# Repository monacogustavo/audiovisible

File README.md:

# audiovisible
An Audiovisual Spectrum Analyzer, for an Underserved Audience

# Features
## CORE
Multi-color display
Audio output

## ADVANCED
Waveform Simulation
Graphic Equalization

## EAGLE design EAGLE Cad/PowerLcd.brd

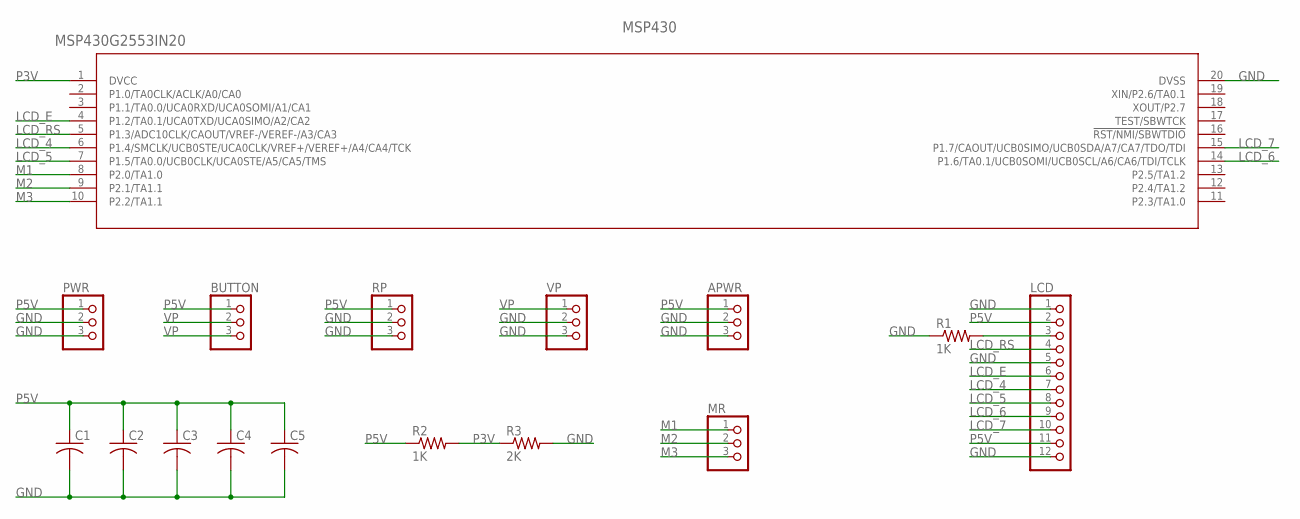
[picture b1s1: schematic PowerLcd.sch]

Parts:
APWR: PINHD-1X3; 1X03
BUTTON: PINHD-1X3; 1X03
C1, C2, C3, C4, C5: C-US075-042X103; C075-042X103
LCD: PINHD-1X12; 1X12
MR: PINHD-1X3; 1X03
MSP430: MSP430G2553IN20; N20_TEX
PWR: PINHD-1X3; 1X03
R1, R2: 1K; 0204/5
R3: 2K; 0204/5
RP: PINHD-1X3; 1X03
VP: PINHD-1X3; 1X03

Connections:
GND: APWR.2, APWR.3, C1.2, C2.2, C3.2, C4.2, C5.2, LCD.1, LCD.5, LCD.12, MSP430.20 (DVSS), PWR.2, PWR.3, R1.1, R3.2, RP.2, RP.3, VP.2, VP.3
LCD_4: LCD.7, MSP430.6 (P1.4/SMCLK/UCB0STE/UCA0CLK/VREF+/VEREF+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)
LCD_5: LCD.8, MSP430.7 (P1.5/TA0.0/UCB0CLK/UCA0STE/A5/CA5/TMS)
LCD_6: LCD.9, MSP430.14 (P1.6/TA0.1/UCB0SOMI/UCB0SCL/A6/CA6/TDI/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)
LCD_7: LCD.10, MSP430.15 (P1.7/CAOUT/UCB0SIMO/UCB0SDA/A7/CA7/TDO/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)
LCD_E: LCD.6, MSP430.4 (P1.2/TA0.1/UCA0TXD/UCA0SIMO/A2/CA2)
LCD_RS: LCD.4, MSP430.5 (P1.3/ADC10CLK/CAOUT/VREF-/VEREF-/A3/CA3)
M1: MR.1, MSP430.8 (P2.0/TA1.0)
M2: MR.2, MSP430.9 (P2.1/TA1.1)
M3: MR.3, MSP430.10 (P2.2/TA1.1)
unnamed: LCD.3, R1.2
P3V: MSP430.1 (DVCC), R2.2, R3.1
P5V: APWR.1, BUTTON.1, C1.1, C2.1, C3.1, C4.1, C5.1, LCD.2, LCD.11, PWR.1, R2.1, RP.1
VP: BUTTON.2, BUTTON.3, VP.1

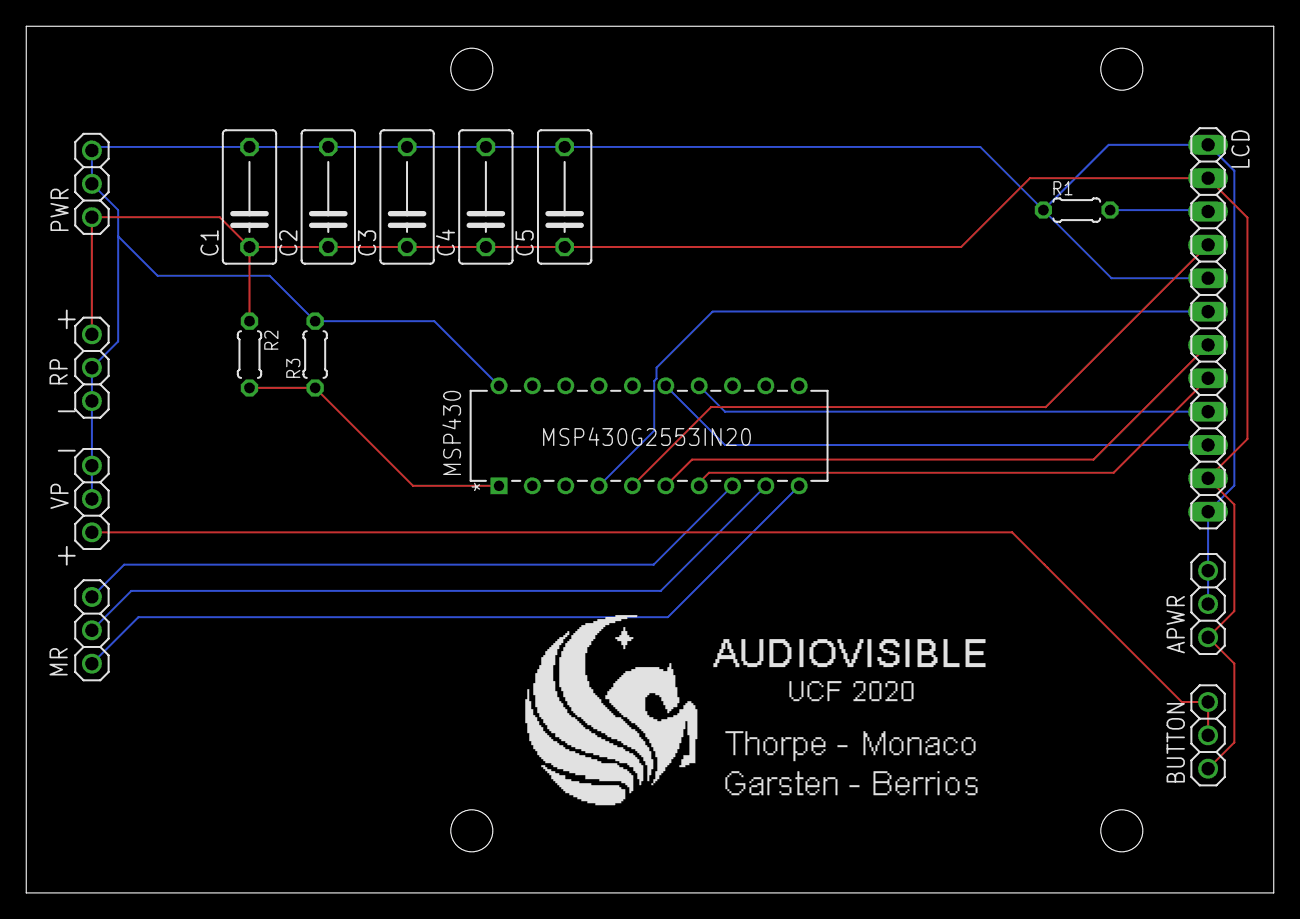
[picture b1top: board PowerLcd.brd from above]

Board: 2 copper layers, 95.0 x 66.0 mm, 20 parts (0 on the bottom side), 14 nets.

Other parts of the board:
U$1, U$2, U$7, U$8: 3_2_HOLE

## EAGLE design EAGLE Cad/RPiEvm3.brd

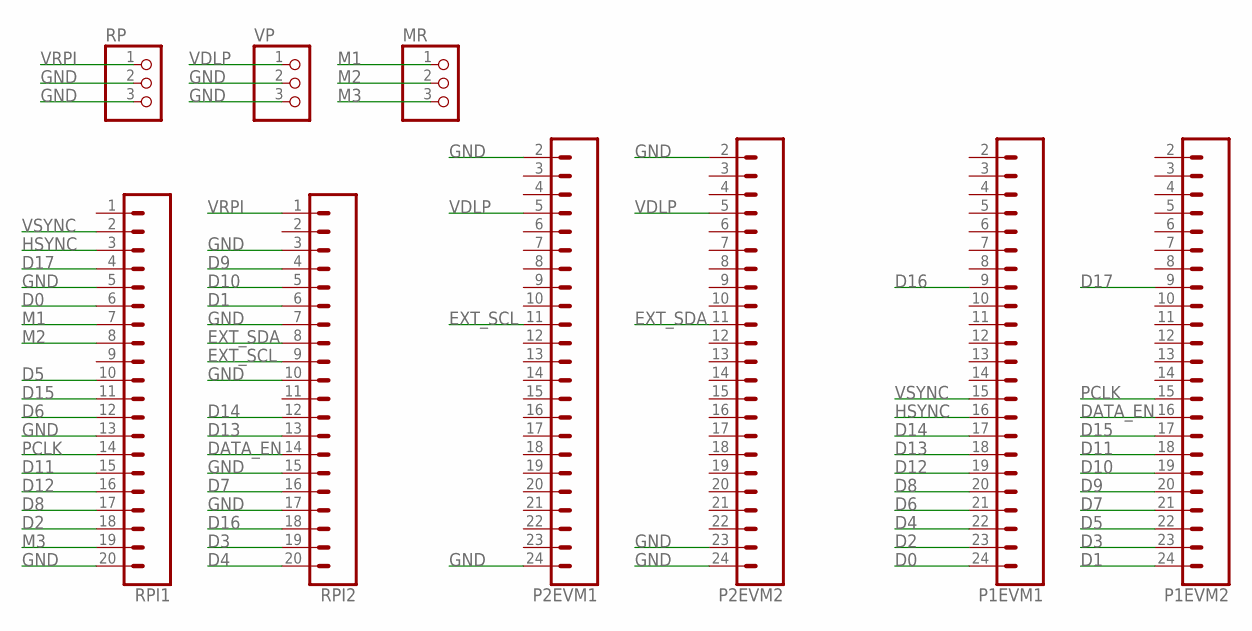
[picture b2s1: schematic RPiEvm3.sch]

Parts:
MR: PINHD-1X3; 1X03
P1EVM1, P1EVM2, P2EVM1, P2EVM2: CONN_23; 1X23
RP: PINHD-1X3; 1X03
RPI1, RPI2: CONN_20; 1X20
VP: PINHD-1X3; 1X03

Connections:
D0: P1EVM1.24, RPI1.6
D1: P1EVM2.24, RPI2.6
D2: P1EVM1.23, RPI1.18
D3: P1EVM2.23, RPI2.19
D4: P1EVM1.22, RPI2.20
D5: P1EVM2.22, RPI1.10
D6: P1EVM1.21, RPI1.12
D7: P1EVM2.21, RPI2.16
D8: P1EVM1.20, RPI1.17
D9: P1EVM2.20, RPI2.4
D10: P1EVM2.19, RPI2.5
D11: P1EVM2.18, RPI1.15
D12: P1EVM1.19, RPI1.16
D13: P1EVM1.18, RPI2.13
D14: P1EVM1.17, RPI2.12
D15: P1EVM2.17, RPI1.11
D16: P1EVM1.9, RPI2.18
D17: P1EVM2.9, RPI1.4
DATA_EN: P1EVM2.16, RPI2.14
EXT_SCL: P2EVM1.11, RPI2.9
EXT_SDA: P2EVM2.11, RPI2.8
GND: P2EVM1.2, P2EVM1.24, P2EVM2.2, P2EVM2.23, P2EVM2.24, RP.2, RP.3, RPI1.5, RPI1.13, RPI1.20, RPI2.3, RPI2.7, RPI2.10, RPI2.15, RPI2.17, VP.2, VP.3
HSYNC: P1EVM1.16, RPI1.3
M1: MR.1, RPI1.7
M2: MR.2, RPI1.8
M3: MR.3, RPI1.19
PCLK: P1EVM2.15, RPI1.14
VDLP: P2EVM1.5, P2EVM2.5, VP.1
VRPI: RP.1, RPI2.1
VSYNC: P1EVM1.15, RPI1.2

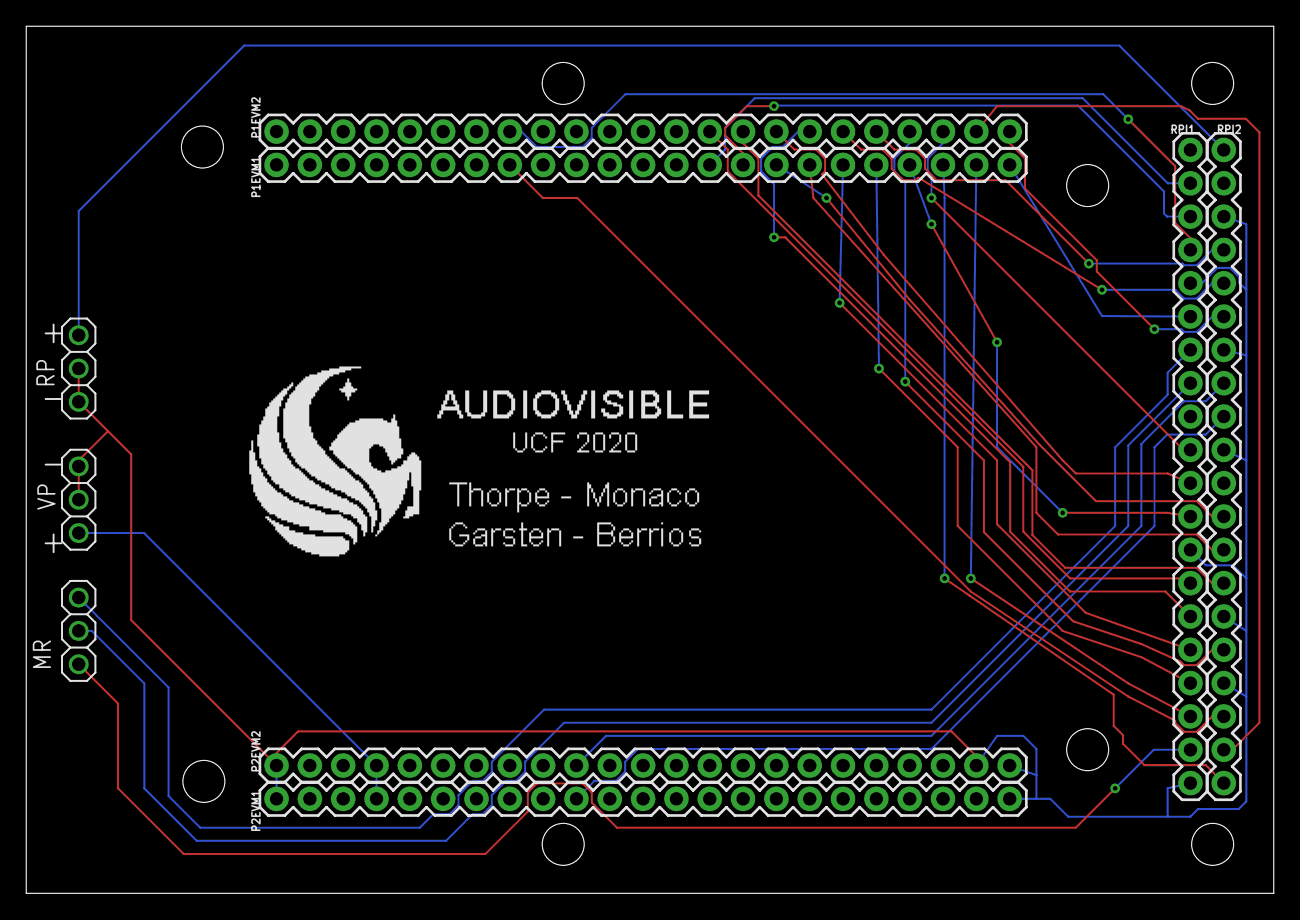
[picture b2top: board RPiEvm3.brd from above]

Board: 2 copper layers, 95.1 x 66.1 mm, 17 parts (0 on the bottom side), 30 nets.

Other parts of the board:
U$1, U$2, U$3, U$4, U$5, U$6, U$7, U$8: 3_2_HOLE

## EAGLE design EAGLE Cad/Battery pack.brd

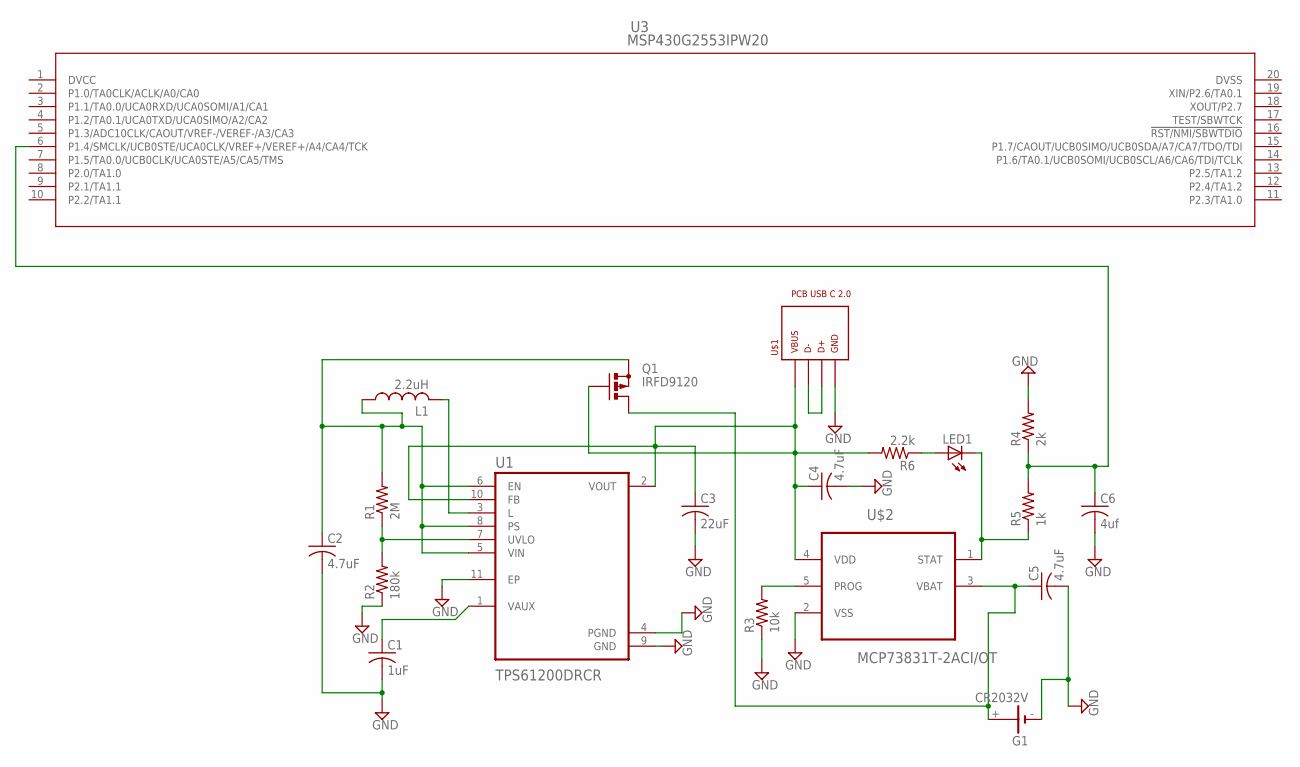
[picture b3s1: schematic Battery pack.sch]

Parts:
C1: 1uF; C150-064X183
C2, C4, C5: 4.7uF; C150-064X183
C3: 22uF; C150-064X183
C6: 4uf; C150-064X183
G1: CR2032V
L1: 2.2uH; 0207/15
LED1: LEDB155; Q62902-B155
Q1: IRFD9120; C370-01
R1: 2M; 0207/15
R2: 180k; 0207/15
R3: 10k; 0207/15
R4: 2k; 0207/15
R5: 1k; 0207/15
R6: 2.2k; 0207/15
U1: TPS61200DRCR; VREG_V62/16624-01YE
U3: MSP430G2553IPW20; PW20
U$1: PCB_USB_C_2.0DS_1; USB_TYPE_C_DS_1
U$2: MCP73831T-2ACI/OT; SOT95P280X145-5N

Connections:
DVCC: U3.1 (DVCC)
DVSS: U3.20 (DVSS)
GND: C1.2, C2.2, C3.2, C4.2, C5.2, C6.2, G1.-, R2.1, R3.1, R4.2, U1.4 (PGND), U1.9 (GND), U1.11 (EP), U$1.A1 (GND), U$1.A12 (GND), U$1.B1 (GND), U$1.B12 (GND), U$2.2 (VSS)
unnamed: R1.1, R2.2, U1.7 (UVLO)
unnamed: C3.1, C4.1, Q1.G, R6.2, U1.2 (VOUT), U1.10 (FB), U$1.A4 (VBUS), U$1.A9 (VBUS), U$1.B4 (VBUS), U$1.B9 (VBUS), U$2.4 (VDD)
unnamed: C2.1, L1.1, Q1.S, R1.2, U1.5 (VIN), U1.6 (EN), U1.8 (PS)
unnamed: C1.1, U1.1 (VAUX)
unnamed: L1.2, U1.3 (L)
unnamed: U$1.A6 (D+), U$1.A7 (D-), U$1.B6 (D+), U$1.B7 (D-)
unnamed: R3.2, U$2.5 (PROG)
unnamed: LED1.K (C), R5.1, U$2.1 (STAT)
unnamed: C6.1, R4.1, R5.2, U3.6 (P1.4/SMCLK/UCB0STE/UCA0CLK/VREF+/VEREF+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)
unnamed: LED1.A, R6.1
unnamed: C5.1, G1.+, Q1.D, Q1.D1 (D), U$2.3 (VBAT)

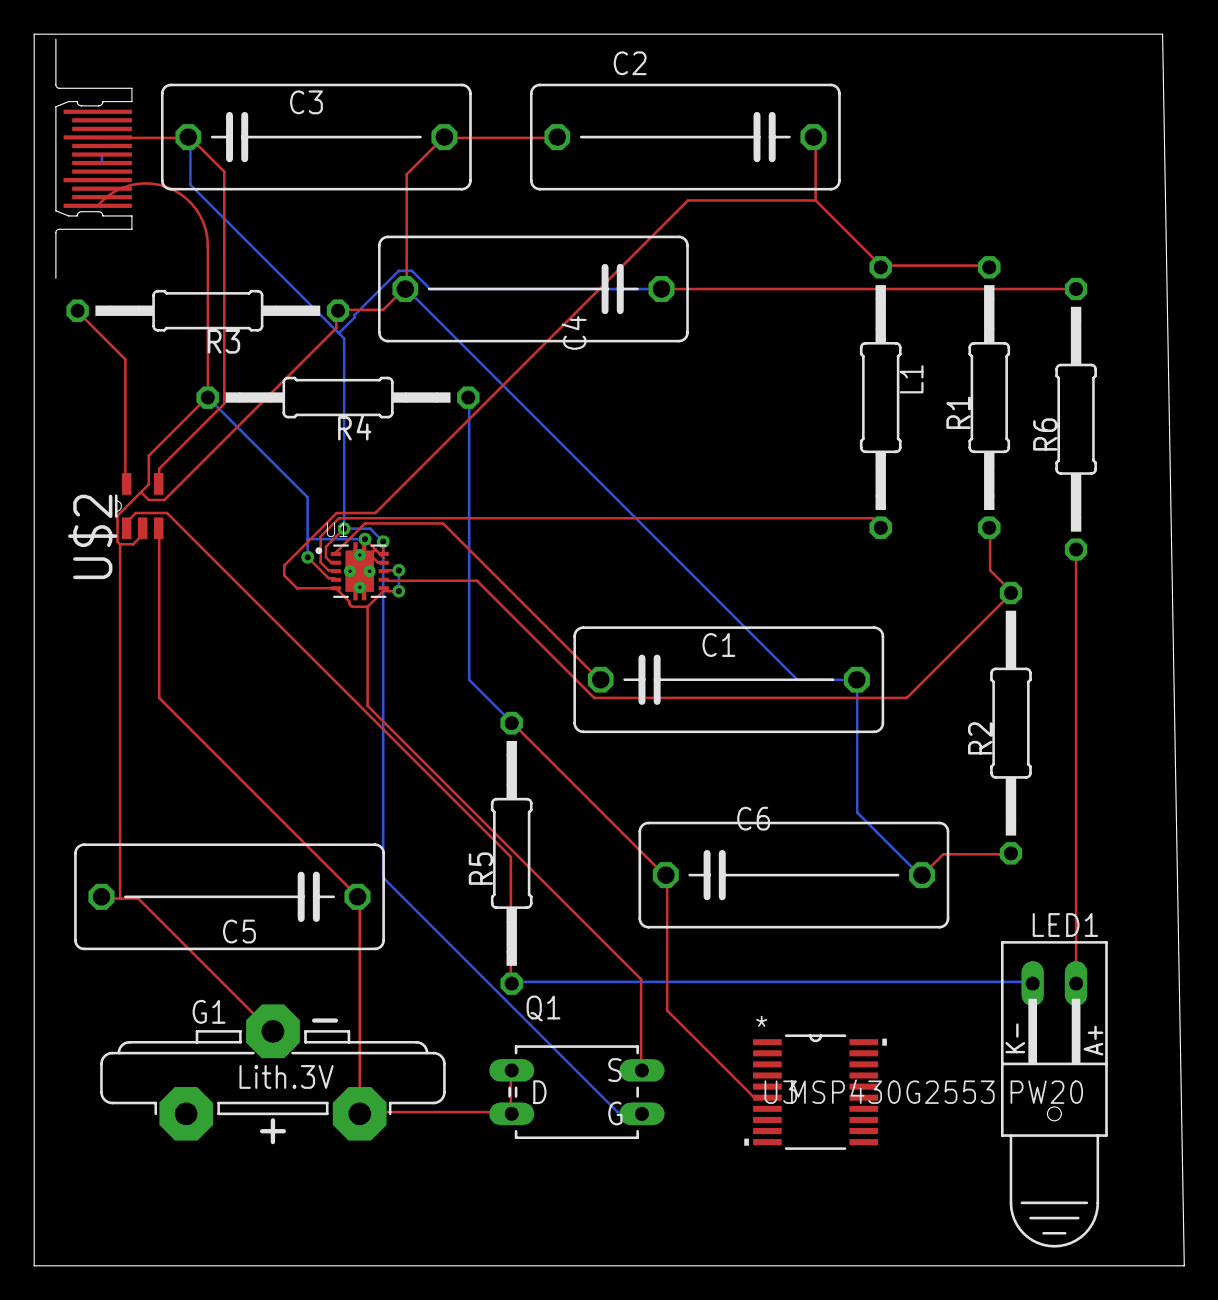
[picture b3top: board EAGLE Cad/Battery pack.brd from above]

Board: 2 copper layers, 67.3 x 72.1 mm, 20 parts (0 on the bottom side), 12 nets.

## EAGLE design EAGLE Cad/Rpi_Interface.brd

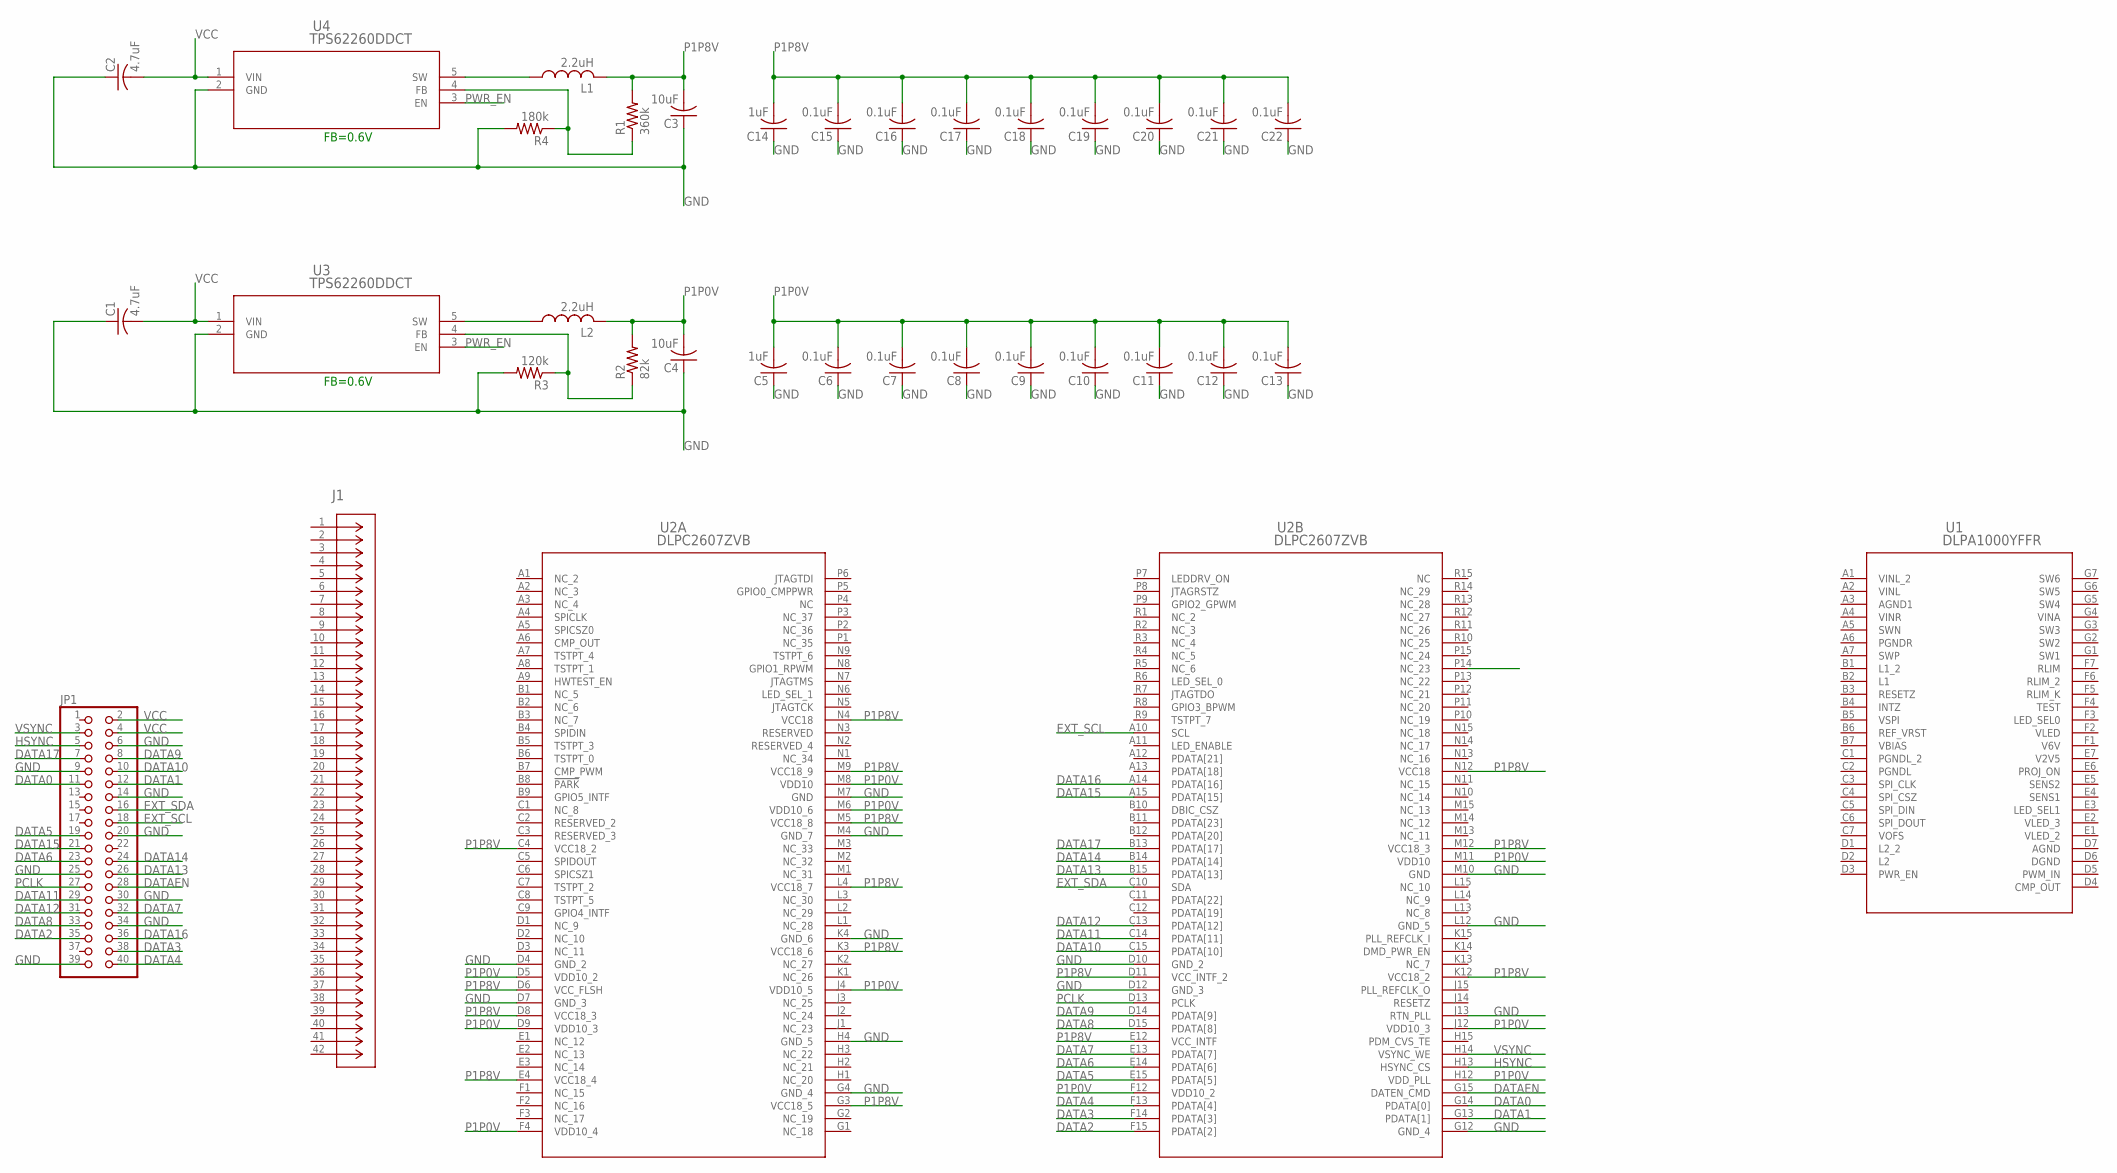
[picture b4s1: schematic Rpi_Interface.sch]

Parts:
C1, C2: 4.7uF; C0201
C3, C4: 10uF; C0201
C5, C14: 1uF; C0201
C6, C7, C8, C9, C10, C11, C12, C13, C15, C16, C17, C18, C19, C20, C21, C22: 0.1uF; C0201
J1: AXT642124DD1; CONN_AXT642124_PAN
JP1: PINHD-2X20; 2X20
L1, L2: 2.2uH; L0201
R1: 360k; 0204V
R2: 82k; 0204V
R3: 120k; 0204V
R4: 180k; 0204V
U1: DLPA1000YFFR; YFF49_TEX
U2: DLPC2607ZVB; ZVB176_TEX
U3, U4: TPS62260DDCT; DDC5

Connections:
AGND: U1.D7 (AGND)
AGND1: U1.A3 (AGND1)
DATA0: JP1.11, U2.G14 (PDATA[0])
DATA1: JP1.12, U2.G13 (PDATA[1])
DATA2: JP1.35, U2.F15 (PDATA[2])
DATA3: JP1.38, U2.F14 (PDATA[3])
DATA4: JP1.40, U2.F13 (PDATA[4])
DATA5: JP1.19, U2.E15 (PDATA[5])
DATA6: JP1.23, U2.E14 (PDATA[6])
DATA7: JP1.32, U2.E13 (PDATA[7])
DATA8: JP1.33, U2.D15 (PDATA[8])
DATA9: JP1.8, U2.D14 (PDATA[9])
DATA10: JP1.10, U2.C15 (PDATA[10])
DATA11: JP1.29, U2.C14 (PDATA[11])
DATA12: JP1.31, U2.C13 (PDATA[12])
DATA13: JP1.26, U2.B15 (PDATA[13])
DATA14: JP1.24, U2.B14 (PDATA[14])
DATA15: JP1.21, U2.A15 (PDATA[15])
DATA16: JP1.36, U2.A14 (PDATA[16])
DATA17: JP1.7, U2.B13 (PDATA[17])
DATAEN: JP1.28, U2.G15 (DATEN_CMD)
DGND: U1.D6 (DGND)
EXT_SCL: JP1.18, U2.A10 (SCL)
EXT_SDA: JP1.16, U2.C10 (SDA)
GND: C1.1, C2.1, C3.1, C4.1, C5.1, C6.1, C7.1, C8.1, C9.1, C10.1, C11.1, C12.1, C13.1, C14.1, C15.1, C16.1, C17.1, C18.1, C19.1, C20.1, C21.1, C22.1, JP1.6, JP1.9, JP1.14, JP1.20, JP1.25, JP1.30, JP1.34, JP1.39, R3.2, R4.2, U2.D4 (GND_2), U2.D7 (GND_3), U2.D10 (GND_2), U2.D12 (GND_3), U2.G4 (GND_4), U2.G12 (GND_4), U2.H4 (GND_5), U2.J13 (RTN_PLL), U2.K4 (GND_6), U2.L12 (GND_5), U2.M4 (GND_7), U2.M7 (GND), U2.M10 (GND), U3.2 (GND), U4.2 (GND)
HSYNC: JP1.5, U2.H13 (HSYNC_CS)
unnamed: R1.1, R4.1, U4.4 (FB)
unnamed: L2.1, U3.5 (SW)
unnamed: L1.1, U4.5 (SW)
unnamed: R2.1, R3.1, U3.4 (FB)
P1P0V: C4.2, C5.2, C6.2, C7.2, C8.2, C9.2, C10.2, C11.2, C12.2, C13.2, L2.2, R2.2, U2.D5 (VDD10_2), U2.D9 (VDD10_3), U2.F4 (VDD10_4), U2.F12 (VDD10_2), U2.H12 (VDD_PLL), U2.J4 (VDD10_5), U2.J12 (VDD10_3), U2.M6 (VDD10_6), U2.M8 (VDD10), U2.M11 (VDD10)
P1P8V: C3.2, C14.2, C15.2, C16.2, C17.2, C18.2, C19.2, C20.2, C21.2, C22.2, L1.2, R1.2, U2.C4 (VCC18_2), U2.D6 (VCC_FLSH), U2.D8 (VCC18_3), U2.D11 (VCC_INTF_2), U2.E4 (VCC18_4), U2.E12 (VCC_INTF), U2.G3 (VCC18_5), U2.K3 (VCC18_6), U2.K12 (VCC18_2), U2.L4 (VCC18_7), U2.M5 (VCC18_8), U2.M9 (VCC18_9), U2.M12 (VCC18_3), U2.N4 (VCC18), U2.N12 (VCC18)
PCLK: JP1.27, U2.D13 (PCLK)
PGNDL: U1.C2 (PGNDL)
PGNDL_2: U1.C1 (PGNDL_2)
PGNDR: U1.A6 (PGNDR)
PWR_EN: U3.3 (EN), U4.3 (EN)
VCC: C1.2, C2.2, JP1.2, JP1.4, U3.1 (VIN), U4.1 (VIN)
VSPI: U1.B5 (VSPI)
VSYNC: JP1.3, U2.H14 (VSYNC_WE)

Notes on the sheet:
FB=0.6V

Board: 2 copper layers, 34 parts (0 on the bottom side), 33 nets, no tracks yet.

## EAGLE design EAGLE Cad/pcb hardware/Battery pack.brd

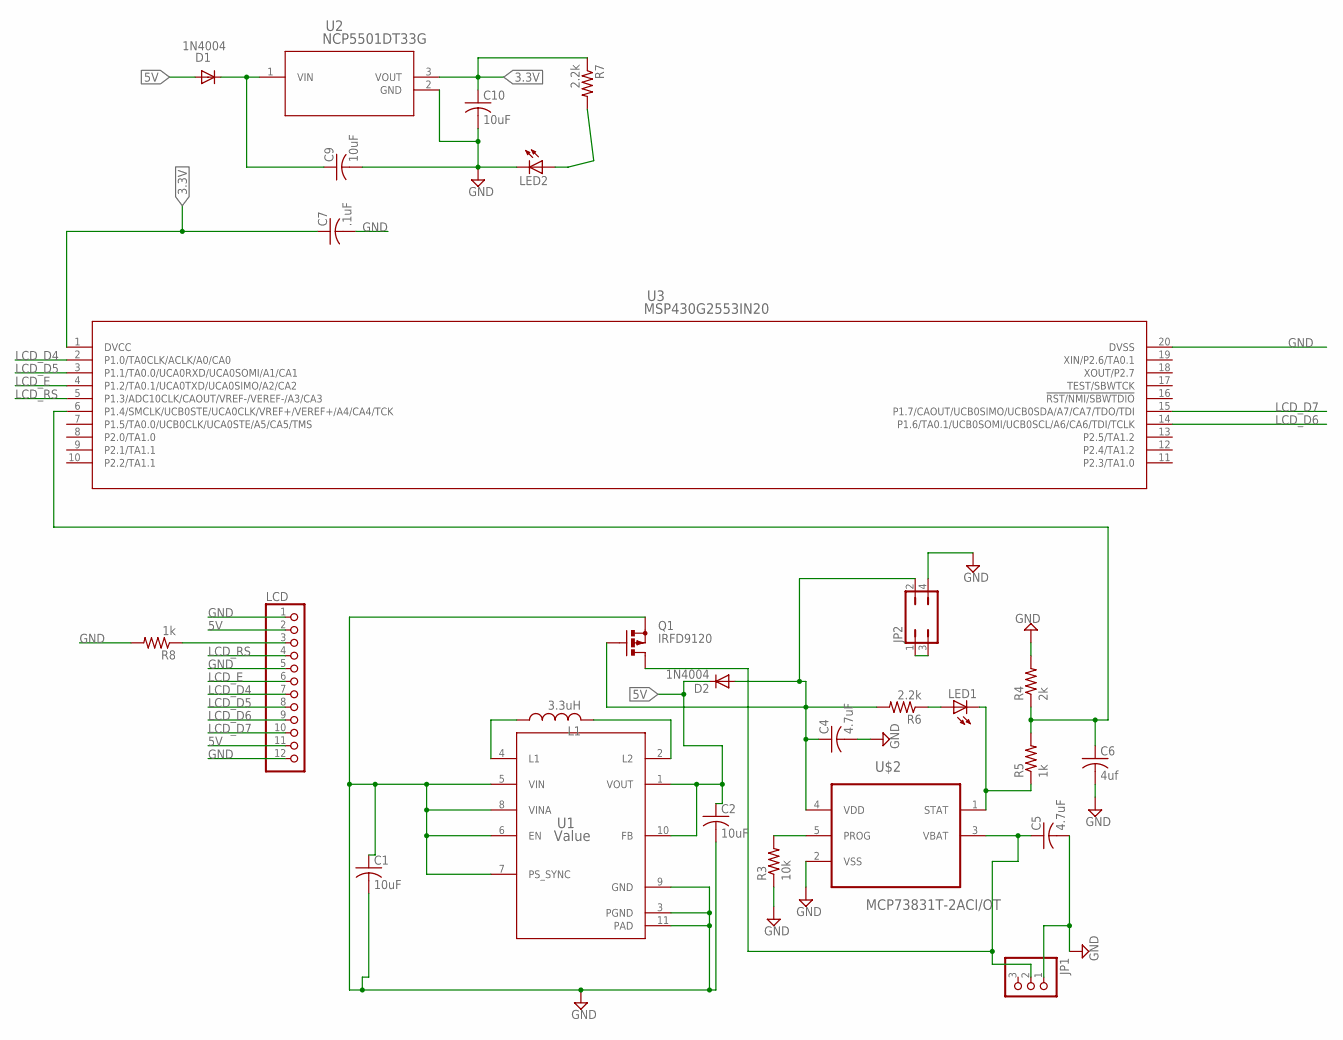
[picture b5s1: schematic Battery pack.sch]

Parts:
C1, C2, C9, C10: 10uF; C150-064X183
C4, C5: 4.7uF; C150-064X183
C6: 4uf; C150-064X183
C7: .1uF; C150-064X183
D1, D2: 1N4004; DO41-10
JP1: PINHD-1X3; 1X03
JP2: JP2Q
L1: 3.3uH; 0207/15
LCD: PINHD-1X12; 1X12
LED1, LED2: LEDB155; Q62902-B155
Q1: IRFD9120; C370-01
R3: 10k; 0207/15
R4: 2k; 0207/15
R5, R8: 1k; 0207/15
R6, R7: 2.2k; 0207/15
U1: Value; DRC0010J
U2: NCP5501DT33G; DPAK-3_ONS
U3: MSP430G2553IN20; N20_TEX
U$2: MCP73831T-2ACI/OT; SOT95P280X145-5N

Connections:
3.3V: C7.1, C10.1, R7.1, U2.3 (VOUT), U3.1 (DVCC)
5V: C2.1, D1.A, D2.C, LCD.2, LCD.11, U1.1 (VOUT), U1.10 (FB)
GND: C1.1, C1.2, C2.2, C4.2, C5.2, C6.2, C7.2, C9.2, C10.2, JP1.1, JP2.4, LCD.1, LCD.5, LCD.12, LED2.K (C), Q1.S, R3.1, R4.2, R8.2, U1.3 (PGND), U1.5 (VIN), U1.6 (EN), U1.7 (PS_SYNC), U1.8 (VINA), U1.9 (GND), U1.11 (PAD), U2.2 (GND), U3.20 (DVSS), U$2.2 (VSS)
LCD_D4: LCD.7, U3.2 (P1.0/TA0CLK/ACLK/A0/CA0)
LCD_D5: LCD.8, U3.3 (P1.1/TA0.0/UCA0RXD/UCA0SOMI/A1/CA1)
LCD_D6: LCD.9, U3.14 (P1.6/TA0.1/UCB0SOMI/UCB0SCL/A6/CA6/TDI/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)
LCD_D7: LCD.10, U3.15 (P1.7/CAOUT/UCB0SIMO/UCB0SDA/A7/CA7/TDO/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)
LCD_E: LCD.6, U3.4 (P1.2/TA0.1/UCA0TXD/UCA0SIMO/A2/CA2)
LCD_RS: LCD.4, U3.5 (P1.3/ADC10CLK/CAOUT/VREF-/VEREF-/A3/CA3)
unnamed: L1.1, U1.4 (L1)
unnamed: C4.1, D2.A, JP2.2, Q1.G, R6.2, U$2.4 (VDD)
unnamed: JP2.1, JP2.3
unnamed: L1.2, U1.2 (L2)
unnamed: C9.1, D1.C, U2.1 (VIN)
unnamed: R3.2, U$2.5 (PROG)
unnamed: LED1.K (C), R5.1, U$2.1 (STAT)
unnamed: C6.1, R4.1, R5.2, U3.6 (P1.4/SMCLK/UCB0STE/UCA0CLK/VREF+/VEREF+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)
unnamed: LED1.A, R6.1
unnamed: C5.1, JP1.2, Q1.D, Q1.D1 (D), U$2.3 (VBAT)
unnamed: LED2.A, R7.2
unnamed: LCD.3, R8.1

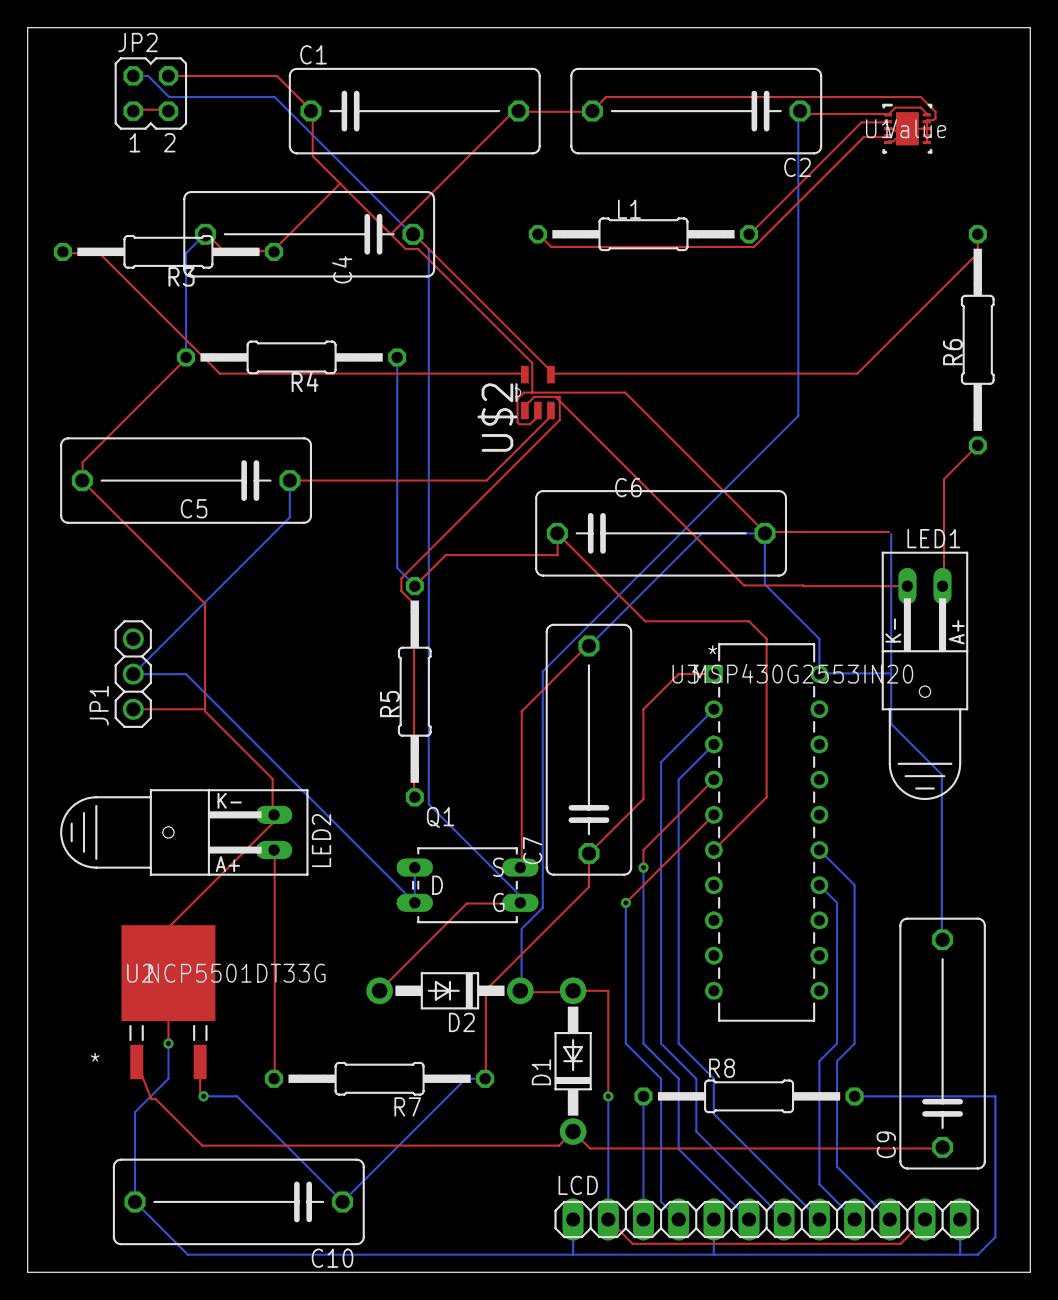
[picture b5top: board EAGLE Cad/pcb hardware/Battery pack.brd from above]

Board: 2 copper layers, 72.4 x 89.8 mm, 27 parts (0 on the bottom side), 21 nets.

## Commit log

2020-12-06 for public
2020-12-06 eagle cad drawings

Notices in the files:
parts and their libraries:
SparkFun-Connectors: Licensing: Creative Commons ShareAlike 4.0 International - https://creativecommons.org/licenses/by-sa/4.0
COPYRIGHT: Copyright (C) 2018 Accelerated Designs. All rights reserved
COPYRIGHT: Copyright (C) 2016 Accelerated Designs. All rights reserved
